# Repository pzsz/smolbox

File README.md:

# Smolbox thumb & pinky

[Bill of Materials](docs/BOM.md)

[Preparing Brooks board & Soldering tips](docs/brooks_prepare.md)

The Smolbox, a portable arcade controller.

* Based on the Brook Fighting Board 
* Wireless Brook Board version compatible with 
PS3&4, PC, Switch (https://www.brookaccessory.com/detail/41130595/). 
* Zero-Pi Brook Board compatible with 
PS3&2, PC, Switch (no PS4 comparability) (https://www.brookaccessory.com/detail/53169470).
* USB-C port.
* Uses hot-swapable low profile Kailh Choc Red Switches (only Choc switches can be used, full-sized switches will not work).
* Bottom plate made from 1mm brushed stainless steel or 3mm acrylic.

## Thumb version
Ultra portable fighting games controller utilising thumb finger for the jump button.
* Sized 181mm x 73mm and 17mm high (without rubber feet (1mm) and keys). Body made from 3mm acrylic.

## Pinky version
Ultra portable fighting games controller utilising pinky finger for the second jump button.
* Sized 181mm x 61mm and 17mm high (without rubber feet (1mm) and keys). Body made from 3mm acrylic.

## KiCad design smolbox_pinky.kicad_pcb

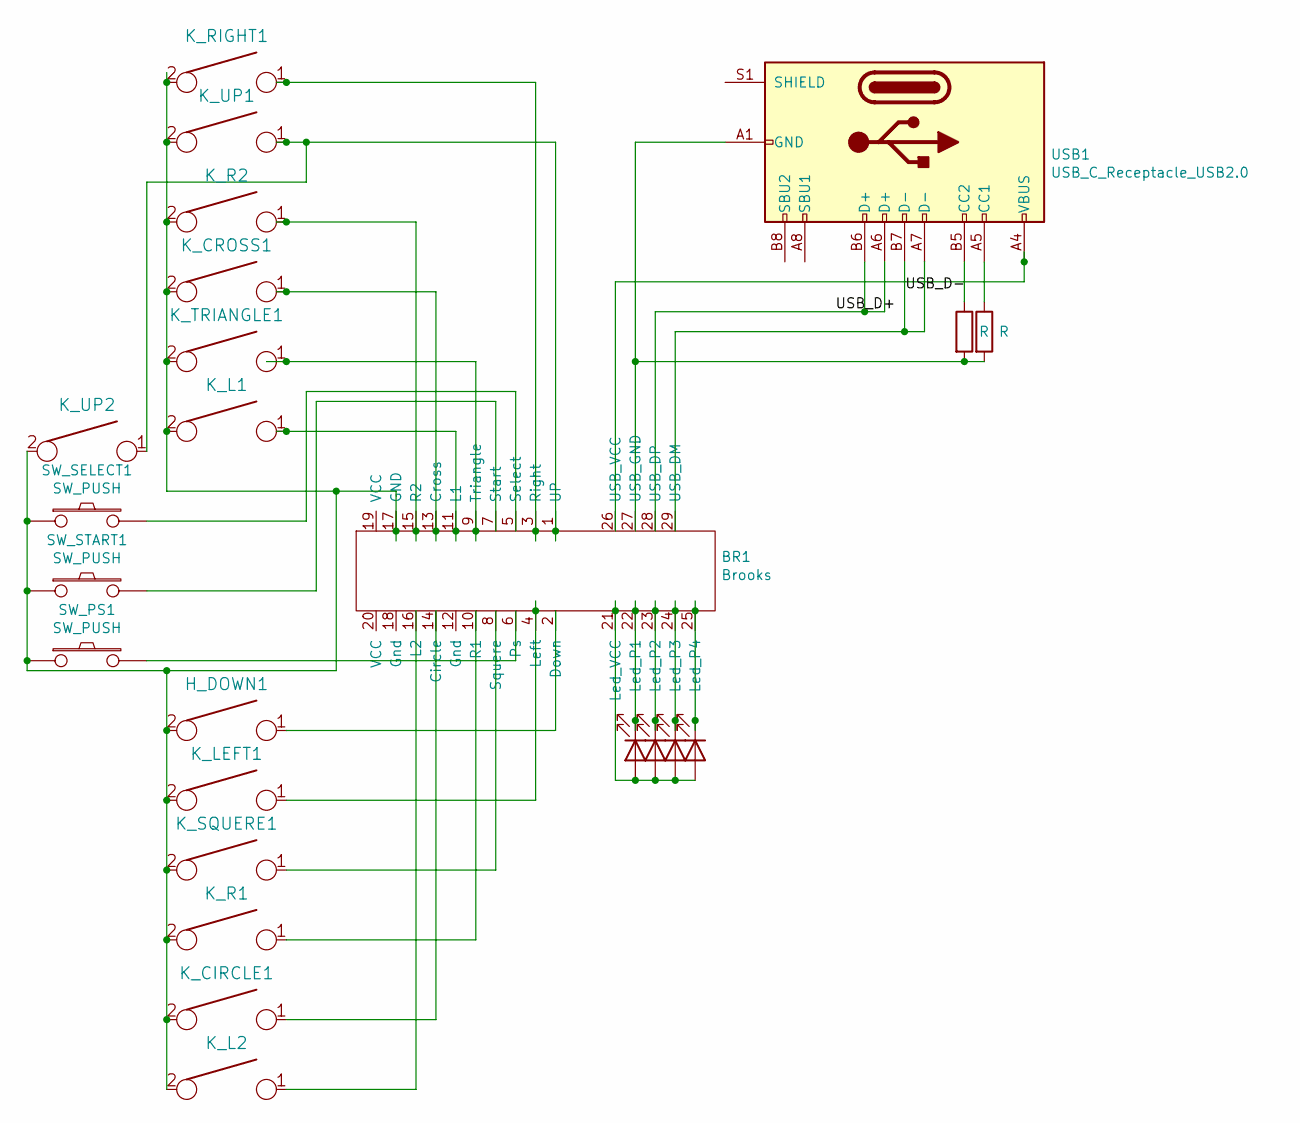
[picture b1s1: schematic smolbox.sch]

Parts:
BR1: Brooks
H_DOWN1: KEYSW; Kailh_socket_PG1350_optional
K_CIRCLE1: KEYSW; Kailh_socket_PG1350_optional
K_CROSS1: KEYSW; Kailh_socket_PG1350_optional
K_L1, K_L2: KEYSW; Kailh_socket_PG1350_optional
K_LEFT1: KEYSW; Kailh_socket_PG1350_optional
K_R1, K_R2: KEYSW; Kailh_socket_PG1350_optional
K_RIGHT1: KEYSW; Kailh_socket_PG1350_optional
K_SQUERE1: KEYSW; Kailh_socket_PG1350_optional
K_TRIANGLE1: KEYSW; Kailh_socket_PG1350_optional
K_UP1, K_UP2: KEYSW; Kailh_socket_PG1350_optional
L_P1, L_P2, L_P3, L_P4: LED; LED_TH
R_cc1, R_cc2: R; R_Axial_DIN0207_L6.3mm_D2.5mm_P10.16mm_Horizontal
SW_PS1: SW_PUSH; SW_PUSH_6mm_hole
SW_SELECT1: SW_PUSH; SW_PUSH_6mm_hole
SW_START1: SW_PUSH; SW_PUSH_6mm_hole
USB1: USB_C_Receptacle_USB2.0; 4085

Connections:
/USB_D+: BR1.28 (USB_DP), USB1.A6 (D+), USB1.B6 (D+)
/USB_D-: BR1.29 (USB_DM), USB1.A7 (D-), USB1.B7 (D-)
unnamed: BR1.1 (UP), K_UP1.1, K_UP2.1
unnamed: BR1.2 (Down), H_DOWN1.1
unnamed: BR1.3 (Right), K_RIGHT1.1
unnamed: BR1.4 (Left), K_LEFT1.1
unnamed: BR1.5 (Select), SW_SELECT1.2
unnamed: BR1.6 (Ps), SW_PS1.2
unnamed: BR1.7 (Start), SW_START1.2
unnamed: BR1.8 (Squere), K_SQUERE1.1
unnamed: BR1.9 (Triangle), K_TRIANGLE1.1
unnamed: BR1.10 (R1), K_R1.1
unnamed: BR1.11 (L1), K_L1.1
unnamed: BR1.13 (Cross), K_CROSS1.1
unnamed: BR1.14 (Circle), K_CIRCLE1.1
unnamed: BR1.15 (R2), K_R2.1
unnamed: BR1.16 (L2), K_L2.1
unnamed: BR1.17 (GND), H_DOWN1.2, K_CIRCLE1.2, K_CROSS1.2, K_L1.2, K_L2.2, K_LEFT1.2, K_R1.2, K_R2.2, K_RIGHT1.2, K_SQUERE1.2, K_TRIANGLE1.2, K_UP1.2, K_UP2.2, SW_PS1.1, SW_SELECT1.1, SW_START1.1
unnamed: BR1.21 (Led_VCC), L_P1.2 (A), L_P2.2 (A), L_P3.2 (A), L_P4.2 (A)
unnamed: BR1.22 (Led_P1), L_P1.1 (K)
unnamed: BR1.23 (Led_P2), L_P2.1 (K)
unnamed: BR1.24 (Led_P3), L_P3.1 (K)
unnamed: BR1.25 (Led_P4), L_P4.1 (K)
unnamed: BR1.26 (USB_VCC), USB1.A4 (VBUS), USB1.A9 (VBUS), USB1.B4 (VBUS), USB1.B9 (VBUS)
unnamed: BR1.27 (USB_GND), R_cc1.2, R_cc2.2, USB1.A1 (GND), USB1.A12 (GND), USB1.B1 (GND), USB1.B12 (GND)
unnamed: R_cc1.1, USB1.A5 (CC1)
unnamed: R_cc2.1, USB1.B5 (CC2)

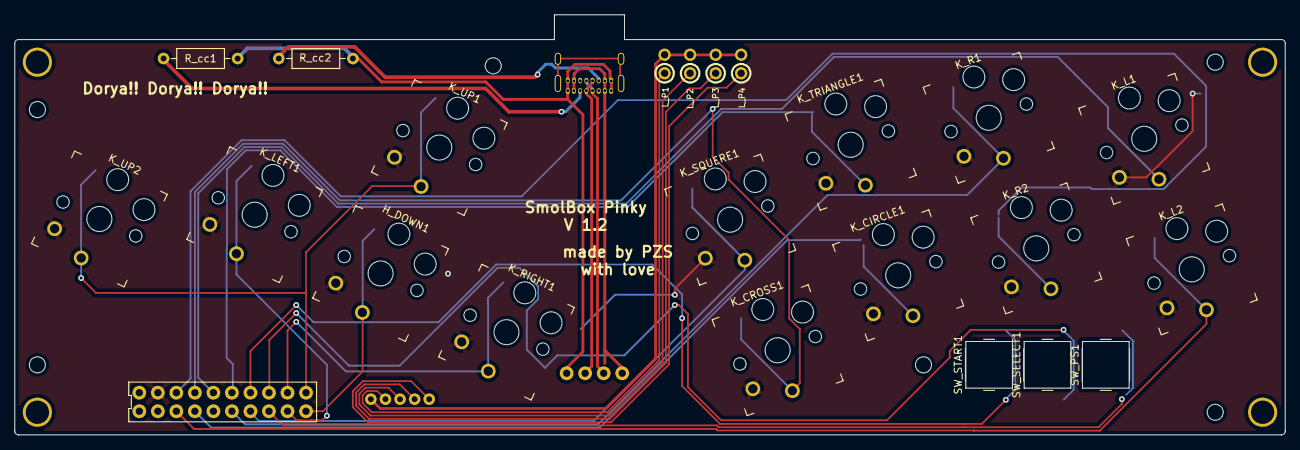
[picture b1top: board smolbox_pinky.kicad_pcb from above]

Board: 2 copper layers, 174.2 x 57.6 mm, 28 parts (1 on the bottom side), 27 nets.

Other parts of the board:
HOLE_M3, HOLE_M3#2, HOLE_M3#3, HOLE_M3#4: H1; HOLE_M3

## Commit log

2021-10-25 Deps and gitignore
2021-10-25 Add kicad_lib_tmk
2021-10-25 Initial version
2021-10-25 Case scad model
2021-10-25 BOM docs
2021-10-25 BOM docs updated with USBC port
2021-10-25 Preparing brooks board
2021-10-25 More docs
